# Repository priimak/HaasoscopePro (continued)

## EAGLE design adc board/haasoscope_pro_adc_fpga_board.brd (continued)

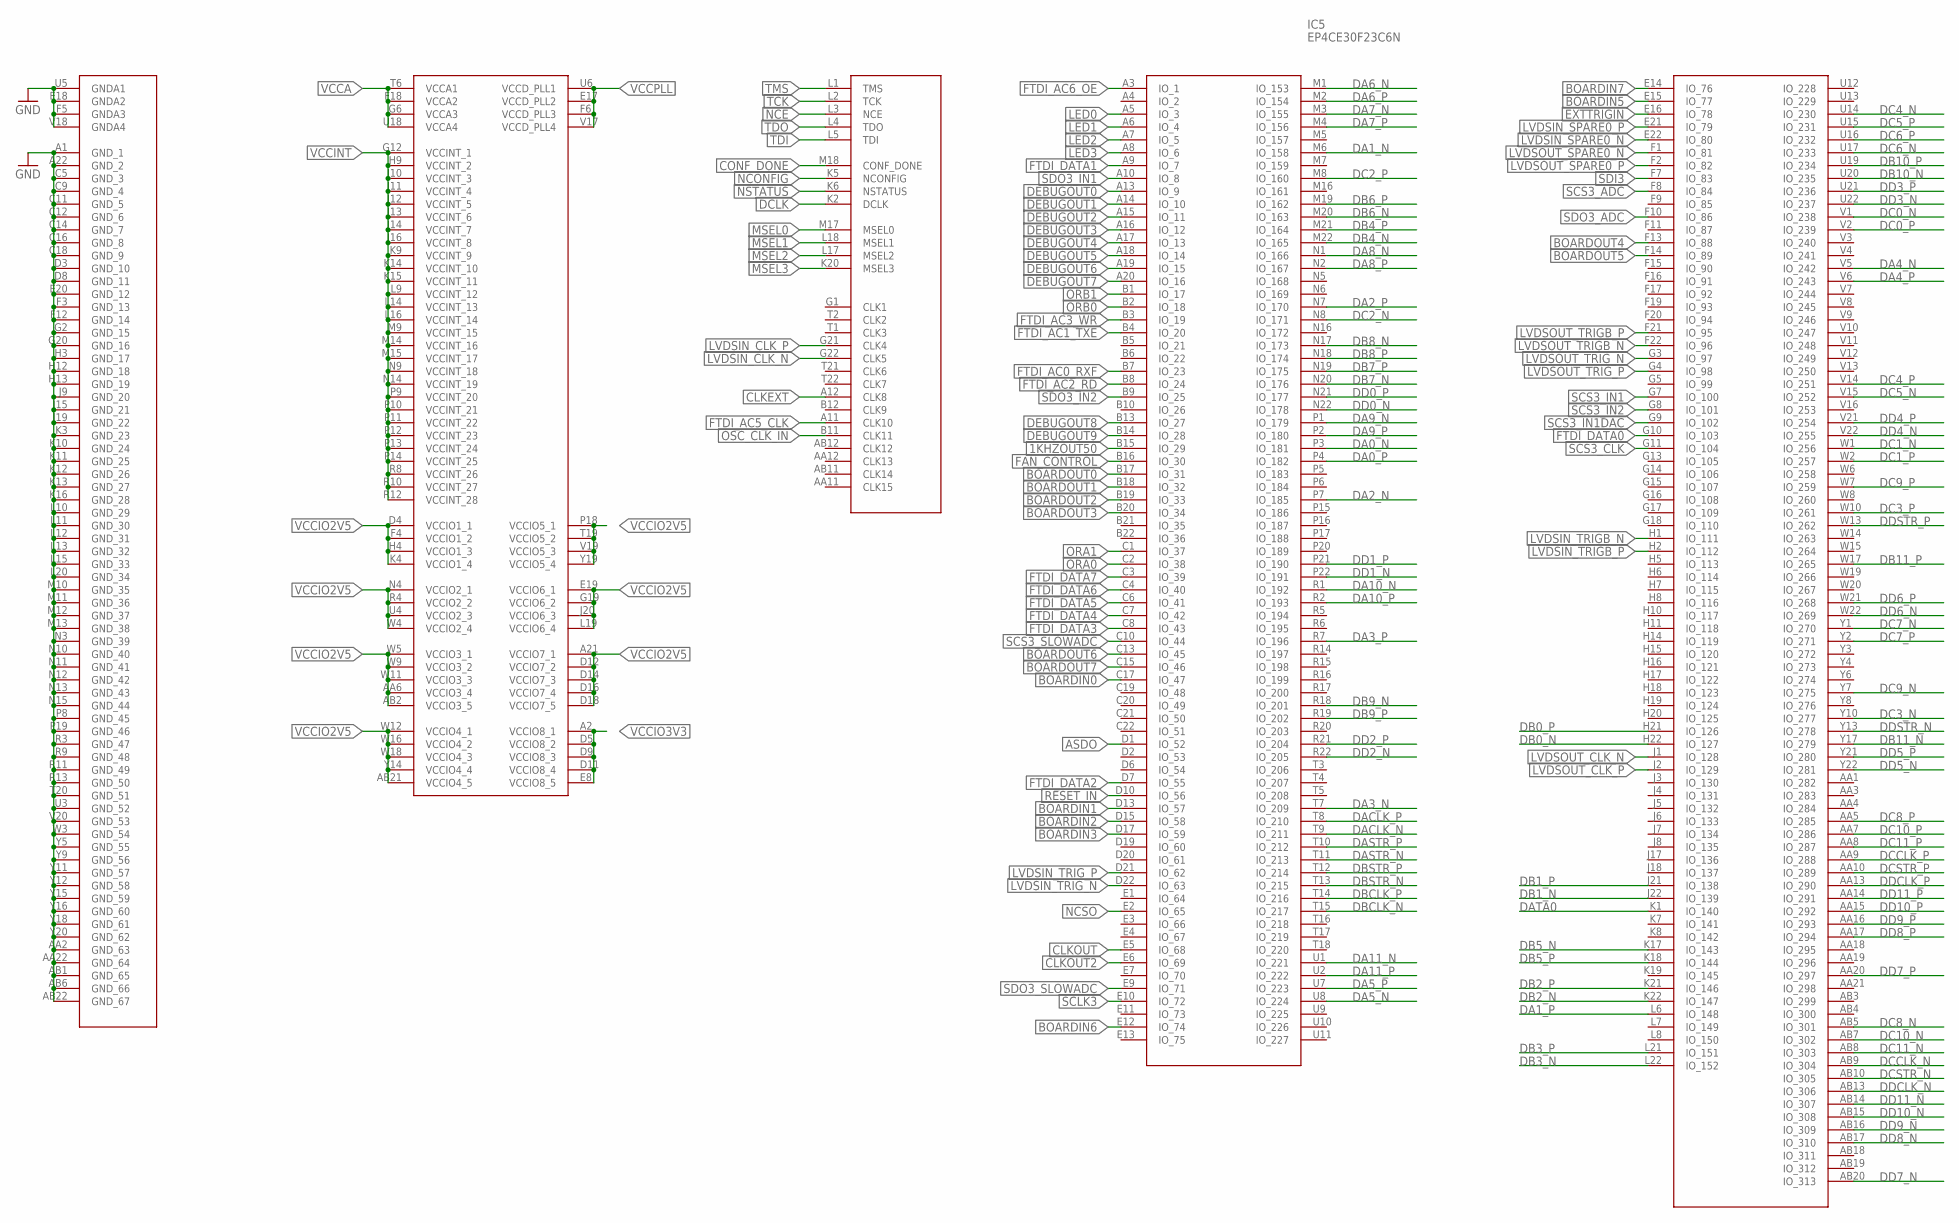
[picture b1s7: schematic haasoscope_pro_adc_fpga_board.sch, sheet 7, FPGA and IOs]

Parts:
IC5: EP4CE30F23C6N; BGA484C100P22X22_2300X2300X240

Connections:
1KHZOUT50: IC5.B15 (IO_29); also elsewhere on the board
ASDO: IC5.D1 (IO_52); also elsewhere on the board
BOARDIN0: IC5.C17 (IO_47); also elsewhere on the board
BOARDIN1: IC5.D13 (IO_57); also elsewhere on the board
BOARDIN2: IC5.D15 (IO_58); also elsewhere on the board
BOARDIN3: IC5.D17 (IO_59); also elsewhere on the board
BOARDIN5: IC5.E15 (IO_77); also elsewhere on the board
BOARDIN6: IC5.E12 (IO_74); also elsewhere on the board
BOARDIN7: IC5.E14 (IO_76); also elsewhere on the board
BOARDOUT0: IC5.B17 (IO_31); also elsewhere on the board
BOARDOUT1: IC5.B18 (IO_32); also elsewhere on the board
BOARDOUT2: IC5.B19 (IO_33); also elsewhere on the board
BOARDOUT3: IC5.B20 (IO_34); also elsewhere on the board
BOARDOUT4: IC5.F13 (IO_88); also elsewhere on the board
BOARDOUT5: IC5.F14 (IO_89); also elsewhere on the board
BOARDOUT6: IC5.C13 (IO_45); also elsewhere on the board
BOARDOUT7: IC5.C15 (IO_46); also elsewhere on the board
CLKEXT: IC5.A12 (CLK8); also elsewhere on the board
CLKOUT: IC5.E5 (IO_68); also elsewhere on the board
CLKOUT2: IC5.E6 (IO_69); also elsewhere on the board
CONF_DONE: IC5.M18 (CONF_DONE); also elsewhere on the board
DA0_N: IC5.P3 (IO_181); also elsewhere on the board
DA0_P: IC5.P4 (IO_182); also elsewhere on the board
DA1_N: IC5.M6 (IO_158); also elsewhere on the board
DA1_P: IC5.L6 (IO_148); also elsewhere on the board
DA2_N: IC5.P7 (IO_185); also elsewhere on the board
DA2_P: IC5.N7 (IO_170); also elsewhere on the board
DA3_N: IC5.T7 (IO_209); also elsewhere on the board
DA3_P: IC5.R7 (IO_196); also elsewhere on the board
DA4_N: IC5.V5 (IO_242); also elsewhere on the board
DA4_P: IC5.V6 (IO_243); also elsewhere on the board
DA5_N: IC5.U8 (IO_224); also elsewhere on the board
DA5_P: IC5.U7 (IO_223); also elsewhere on the board
DA6_N: IC5.M1 (IO_153); also elsewhere on the board
DA6_P: IC5.M2 (IO_154); also elsewhere on the board
DA7_N: IC5.M3 (IO_155); also elsewhere on the board
DA7_P: IC5.M4 (IO_156); also elsewhere on the board
DA8_N: IC5.N1 (IO_166); also elsewhere on the board
DA8_P: IC5.N2 (IO_167); also elsewhere on the board
DA9_N: IC5.P1 (IO_179); also elsewhere on the board
DA9_P: IC5.P2 (IO_180); also elsewhere on the board
DA10_N: IC5.R1 (IO_192); also elsewhere on the board
DA10_P: IC5.R2 (IO_193); also elsewhere on the board
DA11_N: IC5.U1 (IO_221); also elsewhere on the board
DA11_P: IC5.U2 (IO_222); also elsewhere on the board
DACLK_N: IC5.T9 (IO_211); also elsewhere on the board
DACLK_P: IC5.T8 (IO_210); also elsewhere on the board
DASTR_N: IC5.T11 (IO_213); also elsewhere on the board
DASTR_P: IC5.T10 (IO_212); also elsewhere on the board
DATA0: IC5.K1 (IO_140); also elsewhere on the board
DB0_N: IC5.H22 (IO_127); also elsewhere on the board
DB0_P: IC5.H21 (IO_126); also elsewhere on the board
DB1_N: IC5.J22 (IO_139); also elsewhere on the board
DB1_P: IC5.J21 (IO_138); also elsewhere on the board
DB2_N: IC5.K22 (IO_147); also elsewhere on the board
DB2_P: IC5.K21 (IO_146); also elsewhere on the board
DB3_N: IC5.L22 (IO_152); also elsewhere on the board
DB3_P: IC5.L21 (IO_151); also elsewhere on the board
DB4_N: IC5.M22 (IO_165); also elsewhere on the board
DB4_P: IC5.M21 (IO_164); also elsewhere on the board
DB5_N: IC5.K17 (IO_143); also elsewhere on the board
DB5_P: IC5.K18 (IO_144); also elsewhere on the board
DB6_N: IC5.M20 (IO_163); also elsewhere on the board
DB6_P: IC5.M19 (IO_162); also elsewhere on the board
DB7_N: IC5.N20 (IO_176); also elsewhere on the board
DB7_P: IC5.N19 (IO_175); also elsewhere on the board
DB8_N: IC5.N17 (IO_173); also elsewhere on the board
DB8_P: IC5.N18 (IO_174); also elsewhere on the board
DB9_N: IC5.R18 (IO_201); also elsewhere on the board
DB9_P: IC5.R19 (IO_202); also elsewhere on the board
DB10_N: IC5.U20 (IO_235); also elsewhere on the board
DB10_P: IC5.U19 (IO_234); also elsewhere on the board
DB11_N: IC5.Y17 (IO_279); also elsewhere on the board
DB11_P: IC5.W17 (IO_265); also elsewhere on the board
DBCLK_N: IC5.T15 (IO_217); also elsewhere on the board
DBCLK_P: IC5.T14 (IO_216); also elsewhere on the board
DBSTR_N: IC5.T13 (IO_215); also elsewhere on the board
DBSTR_P: IC5.T12 (IO_214); also elsewhere on the board
DC0_N: IC5.V1 (IO_238); also elsewhere on the board
DC0_P: IC5.V2 (IO_239); also elsewhere on the board
DC1_N: IC5.W1 (IO_256); also elsewhere on the board
DC1_P: IC5.W2 (IO_257); also elsewhere on the board
DC2_N: IC5.N8 (IO_171); also elsewhere on the board
DC2_P: IC5.M8 (IO_160); also elsewhere on the board
DC3_N: IC5.Y10 (IO_277); also elsewhere on the board
DC3_P: IC5.W10 (IO_261); also elsewhere on the board
DC4_N: IC5.U14 (IO_230); also elsewhere on the board
DC4_P: IC5.V14 (IO_251); also elsewhere on the board
DC5_N: IC5.V15 (IO_252); also elsewhere on the board
DC5_P: IC5.U15 (IO_231); also elsewhere on the board
DC6_N: IC5.U17 (IO_233); also elsewhere on the board
DC6_P: IC5.U16 (IO_232); also elsewhere on the board
DC7_N: IC5.Y1 (IO_270); also elsewhere on the board
DC7_P: IC5.Y2 (IO_271); also elsewhere on the board
DC8_N: IC5.AB5 (IO_301); also elsewhere on the board
DC8_P: IC5.AA5 (IO_285); also elsewhere on the board
DC9_N: IC5.Y7 (IO_275); also elsewhere on the board
DC9_P: IC5.W7 (IO_259); also elsewhere on the board
DC10_N: IC5.AB7 (IO_302); also elsewhere on the board
DC10_P: IC5.AA7 (IO_286); also elsewhere on the board
DC11_N: IC5.AB8 (IO_303); also elsewhere on the board
DC11_P: IC5.AA8 (IO_287); also elsewhere on the board
DCCLK_N: IC5.AB9 (IO_304); also elsewhere on the board
DCCLK_P: IC5.AA9 (IO_288); also elsewhere on the board
DCLK: IC5.K2 (DCLK); also elsewhere on the board
DCSTR_N: IC5.AB10 (IO_305); also elsewhere on the board
DCSTR_P: IC5.AA10 (IO_289); also elsewhere on the board
DD0_N: IC5.N22 (IO_178); also elsewhere on the board
DD0_P: IC5.N21 (IO_177); also elsewhere on the board
DD1_N: IC5.P22 (IO_191); also elsewhere on the board
DD1_P: IC5.P21 (IO_190); also elsewhere on the board
DD2_N: IC5.R22 (IO_205); also elsewhere on the board
DD2_P: IC5.R21 (IO_204); also elsewhere on the board
DD3_N: IC5.U22 (IO_237); also elsewhere on the board
DD3_P: IC5.U21 (IO_236); also elsewhere on the board
DD4_N: IC5.V22 (IO_255); also elsewhere on the board
DD4_P: IC5.V21 (IO_254); also elsewhere on the board
DD5_N: IC5.Y22 (IO_281); also elsewhere on the board
DD5_P: IC5.Y21 (IO_280); also elsewhere on the board
DD6_N: IC5.W22 (IO_269); also elsewhere on the board
DD6_P: IC5.W21 (IO_268); also elsewhere on the board
DD7_N: IC5.AB20 (IO_313); also elsewhere on the board
DD7_P: IC5.AA20 (IO_297); also elsewhere on the board
DD8_N: IC5.AB17 (IO_310); also elsewhere on the board
DD8_P: IC5.AA17 (IO_294); also elsewhere on the board
DD9_N: IC5.AB16 (IO_309); also elsewhere on the board
DD9_P: IC5.AA16 (IO_293); also elsewhere on the board
DD10_N: IC5.AB15 (IO_308); also elsewhere on the board
DD10_P: IC5.AA15 (IO_292); also elsewhere on the board
DD11_N: IC5.AB14 (IO_307); also elsewhere on the board
DD11_P: IC5.AA14 (IO_291); also elsewhere on the board
DDCLK_N: IC5.AB13 (IO_306); also elsewhere on the board
DDCLK_P: IC5.AA13 (IO_290); also elsewhere on the board
DDSTR_N: IC5.Y13 (IO_278); also elsewhere on the board
DDSTR_P: IC5.W13 (IO_262); also elsewhere on the board
DEBUGOUT0: IC5.A13 (IO_9); also elsewhere on the board
DEBUGOUT1: IC5.A14 (IO_10); also elsewhere on the board
DEBUGOUT2: IC5.A15 (IO_11); also elsewhere on the board
DEBUGOUT3: IC5.A16 (IO_12); also elsewhere on the board
DEBUGOUT4: IC5.A17 (IO_13); also elsewhere on the board
DEBUGOUT5: IC5.A18 (IO_14); also elsewhere on the board
DEBUGOUT6: IC5.A19 (IO_15); also elsewhere on the board
DEBUGOUT7: IC5.A20 (IO_16); also elsewhere on the board
DEBUGOUT8: IC5.B13 (IO_27); also elsewhere on the board
DEBUGOUT9: IC5.B14 (IO_28); also elsewhere on the board
EXTTRIGIN: IC5.E16 (IO_78); also elsewhere on the board
FAN_CONTROL: IC5.B16 (IO_30); also elsewhere on the board
FTDI_AC0_RXF: IC5.B7 (IO_23); also elsewhere on the board
FTDI_AC1_TXE: IC5.B4 (IO_20); also elsewhere on the board
FTDI_AC2_RD: IC5.B8 (IO_24); also elsewhere on the board
FTDI_AC3_WR: IC5.B3 (IO_19); also elsewhere on the board
FTDI_AC5_CLK: IC5.A11 (CLK10); also elsewhere on the board
FTDI_AC6_OE: IC5.A3 (IO_1); also elsewhere on the board
FTDI_DATA0: IC5.G10 (IO_103); also elsewhere on the board
FTDI_DATA1: IC5.A9 (IO_7); also elsewhere on the board
FTDI_DATA2: IC5.D7 (IO_55); also elsewhere on the board
FTDI_DATA3: IC5.C8 (IO_43); also elsewhere on the board
FTDI_DATA4: IC5.C7 (IO_42); also elsewhere on the board
FTDI_DATA5: IC5.C6 (IO_41); also elsewhere on the board
FTDI_DATA6: IC5.C4 (IO_40); also elsewhere on the board
FTDI_DATA7: IC5.C3 (IO_39); also elsewhere on the board
GND: IC5.A1 (GND_1), IC5.A22 (GND_2), IC5.AA2 (GND_63), IC5.AA22 (GND_64), IC5.AB1 (GND_65), IC5.AB6 (GND_66), IC5.AB22 (GND_67), IC5.C5 (GND_3), IC5.C9 (GND_4), IC5.C11 (GND_5), IC5.C12 (GND_6), IC5.C14 (GND_7), IC5.C16 (GND_8), IC5.C18 (GND_9), IC5.D3 (GND_10), IC5.D8 (GND_11), IC5.E18 (GNDA2), IC5.E20 (GND_12), IC5.F3 (GND_13), IC5.F5 (GNDA3), IC5.F12 (GND_14), IC5.G2 (GND_15), IC5.G20 (GND_16), IC5.H3 (GND_17), IC5.H12 (GND_18), IC5.H13 (GND_19), IC5.J9 (GND_20), IC5.J15 (GND_21), IC5.J19 (GND_22), IC5.K3 (GND_23), IC5.K10 (GND_24), IC5.K11 (GND_25), IC5.K12 (GND_26), IC5.K13 (GND_27), IC5.K16 (GND_28), IC5.L10 (GND_29), IC5.L11 (GND_30), IC5.L12 (GND_31), IC5.L13 (GND_32), IC5.L15 (GND_33), IC5.L20 (GND_34), IC5.M10 (GND_35), IC5.M11 (GND_36), IC5.M12 (GND_37), IC5.M13 (GND_38), IC5.N3 (GND_39), IC5.N10 (GND_40), IC5.N11 (GND_41), IC5.N12 (GND_42), IC5.N13 (GND_43), IC5.N15 (GND_44), IC5.P8 (GND_45), IC5.P19 (GND_46), IC5.R3 (GND_47), IC5.R9 (GND_48), IC5.R11 (GND_49), IC5.R13 (GND_50), IC5.T20 (GND_51), IC5.U3 (GND_52), IC5.U5 (GNDA1), IC5.V18 (GNDA4), IC5.V20 (GND_53), IC5.W3 (GND_54), IC5.Y5 (GND_55), IC5.Y9 (GND_56), IC5.Y11 (GND_57), IC5.Y12 (GND_58), IC5.Y15 (GND_59), IC5.Y16 (GND_60), IC5.Y18 (GND_61), IC5.Y20 (GND_62); also elsewhere on the board
LED0: IC5.A5 (IO_3); also elsewhere on the board
LED1: IC5.A6 (IO_4); also elsewhere on the board
LED2: IC5.A7 (IO_5); also elsewhere on the board
LED3: IC5.A8 (IO_6); also elsewhere on the board
LVDSIN_CLK_N: IC5.G22 (CLK5); also elsewhere on the board
LVDSIN_CLK_P: IC5.G21 (CLK4); also elsewhere on the board
LVDSIN_SPARE0_N: IC5.E22 (IO_80); also elsewhere on the board
LVDSIN_SPARE0_P: IC5.E21 (IO_79); also elsewhere on the board
LVDSIN_TRIGB_N: IC5.H1 (IO_111); also elsewhere on the board
LVDSIN_TRIGB_P: IC5.H2 (IO_112); also elsewhere on the board
LVDSIN_TRIG_N: IC5.D22 (IO_63); also elsewhere on the board
LVDSIN_TRIG_P: IC5.D21 (IO_62); also elsewhere on the board
LVDSOUT_CLK_N: IC5.J1 (IO_128); also elsewhere on the board
LVDSOUT_CLK_P: IC5.J2 (IO_129); also elsewhere on the board
LVDSOUT_SPARE0_N: IC5.F1 (IO_81); also elsewhere on the board
LVDSOUT_SPARE0_P: IC5.F2 (IO_82); also elsewhere on the board
LVDSOUT_TRIGB_N: IC5.F22 (IO_96); also elsewhere on the board
LVDSOUT_TRIGB_P: IC5.F21 (IO_95); also elsewhere on the board
LVDSOUT_TRIG_N: IC5.G3 (IO_97); also elsewhere on the board
LVDSOUT_TRIG_P: IC5.G4 (IO_98); also elsewhere on the board
MSEL0: IC5.M17 (MSEL0); also elsewhere on the board
MSEL1: IC5.L18 (MSEL1); also elsewhere on the board
MSEL2: IC5.L17 (MSEL2); also elsewhere on the board
MSEL3: IC5.K20 (MSEL3); also elsewhere on the board
NCE: IC5.L3 (NCE); also elsewhere on the board
NCONFIG: IC5.K5 (NCONFIG); also elsewhere on the board
NCSO: IC5.E2 (IO_65); also elsewhere on the board
NSTATUS: IC5.K6 (NSTATUS); also elsewhere on the board
ORA0: IC5.C2 (IO_38); also elsewhere on the board
ORA1: IC5.C1 (IO_37); also elsewhere on the board
ORB0: IC5.B2 (IO_18); also elsewhere on the board
ORB1: IC5.B1 (IO_17); also elsewhere on the board
OSC_CLK_IN: IC5.B11 (CLK11); also elsewhere on the board
RESET_IN: IC5.D10 (IO_56); also elsewhere on the board
SCLK3: IC5.E10 (IO_72); also elsewhere on the board
SCS3_ADC: IC5.F8 (IO_84); also elsewhere on the board
SCS3_CLK: IC5.G11 (IO_104); also elsewhere on the board
SCS3_IN1: IC5.G7 (IO_100); also elsewhere on the board
SCS3_IN1DAC: IC5.G9 (IO_102); also elsewhere on the board
SCS3_IN2: IC5.G8 (IO_101); also elsewhere on the board
SCS3_SLOWADC: IC5.C10 (IO_44); also elsewhere on the board
SDI3: IC5.F7 (IO_83); also elsewhere on the board
SDO3_ADC: IC5.F10 (IO_86); also elsewhere on the board
SDO3_IN1: IC5.A10 (IO_8); also elsewhere on the board
SDO3_IN2: IC5.B9 (IO_25); also elsewhere on the board
SDO3_SLOWADC: IC5.E9 (IO_71); also elsewhere on the board
TCK: IC5.L2 (TCK); also elsewhere on the board
TDI: IC5.L5 (TDI); also elsewhere on the board
TDO: IC5.L4 (TDO); also elsewhere on the board
TMS: IC5.L1 (TMS); also elsewhere on the board
VCCA: IC5.F18 (VCCA2), IC5.G6 (VCCA3), IC5.T6 (VCCA1), IC5.U18 (VCCA4); also elsewhere on the board
VCCINT: IC5.G12 (VCCINT_1), IC5.H9 (VCCINT_2), IC5.J10 (VCCINT_3), IC5.J11 (VCCINT_4), IC5.J12 (VCCINT_5), IC5.J13 (VCCINT_6), IC5.J14 (VCCINT_7), IC5.J16 (VCCINT_8), IC5.K9 (VCCINT_9), IC5.K14 (VCCINT_10), IC5.K15 (VCCINT_11), IC5.L9 (VCCINT_12), IC5.L14 (VCCINT_13), IC5.L16 (VCCINT_14), IC5.M9 (VCCINT_15), IC5.M14 (VCCINT_16), IC5.M15 (VCCINT_17), IC5.N9 (VCCINT_18), IC5.N14 (VCCINT_19), IC5.P9 (VCCINT_20), IC5.P10 (VCCINT_21), IC5.P11 (VCCINT_22), IC5.P12 (VCCINT_23), IC5.P13 (VCCINT_24), IC5.P14 (VCCINT_25), IC5.R8 (VCCINT_26), IC5.R10 (VCCINT_27), IC5.R12 (VCCINT_28); also elsewhere on the board
VCCIO2V5: IC5.A21 (VCCIO7_1), IC5.AA6 (VCCIO3_4), IC5.AB2 (VCCIO3_5), IC5.AB21 (VCCIO4_5), IC5.D4 (VCCIO1_1), IC5.D12 (VCCIO7_2), IC5.D14 (VCCIO7_3), IC5.D16 (VCCIO7_4), IC5.D18 (VCCIO7_5), IC5.E19 (VCCIO6_1), IC5.F4 (VCCIO1_2), IC5.G19 (VCCIO6_2), IC5.H4 (VCCIO1_3), IC5.J20 (VCCIO6_3), IC5.K4 (VCCIO1_4), IC5.L19 (VCCIO6_4), IC5.N4 (VCCIO2_1), IC5.P18 (VCCIO5_1), IC5.R4 (VCCIO2_2), IC5.T19 (VCCIO5_2), IC5.U4 (VCCIO2_3), IC5.V19 (VCCIO5_3), IC5.W4 (VCCIO2_4), IC5.W5 (VCCIO3_1), IC5.W9 (VCCIO3_2), IC5.W11 (VCCIO3_3), IC5.W12 (VCCIO4_1), IC5.W16 (VCCIO4_2), IC5.W18 (VCCIO4_3), IC5.Y14 (VCCIO4_4), IC5.Y19 (VCCIO5_4); also elsewhere on the board
VCCIO3V3: IC5.A2 (VCCIO8_1), IC5.D5 (VCCIO8_2), IC5.D9 (VCCIO8_3), IC5.D11 (VCCIO8_4), IC5.E8 (VCCIO8_5); also elsewhere on the board
VCCPLL: IC5.E17 (VCCD_PLL2), IC5.F6 (VCCD_PLL3), IC5.U6 (VCCD_PLL1), IC5.V17 (VCCD_PLL4); also elsewhere on the board
